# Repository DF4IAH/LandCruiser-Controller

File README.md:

# LandCruiser-Controller
µP controller for enabling LandCruisers for special tail-gates, alarms and multiple other features based on ATmega328P. Hardware (EAGLE), Software and Documentation is included.

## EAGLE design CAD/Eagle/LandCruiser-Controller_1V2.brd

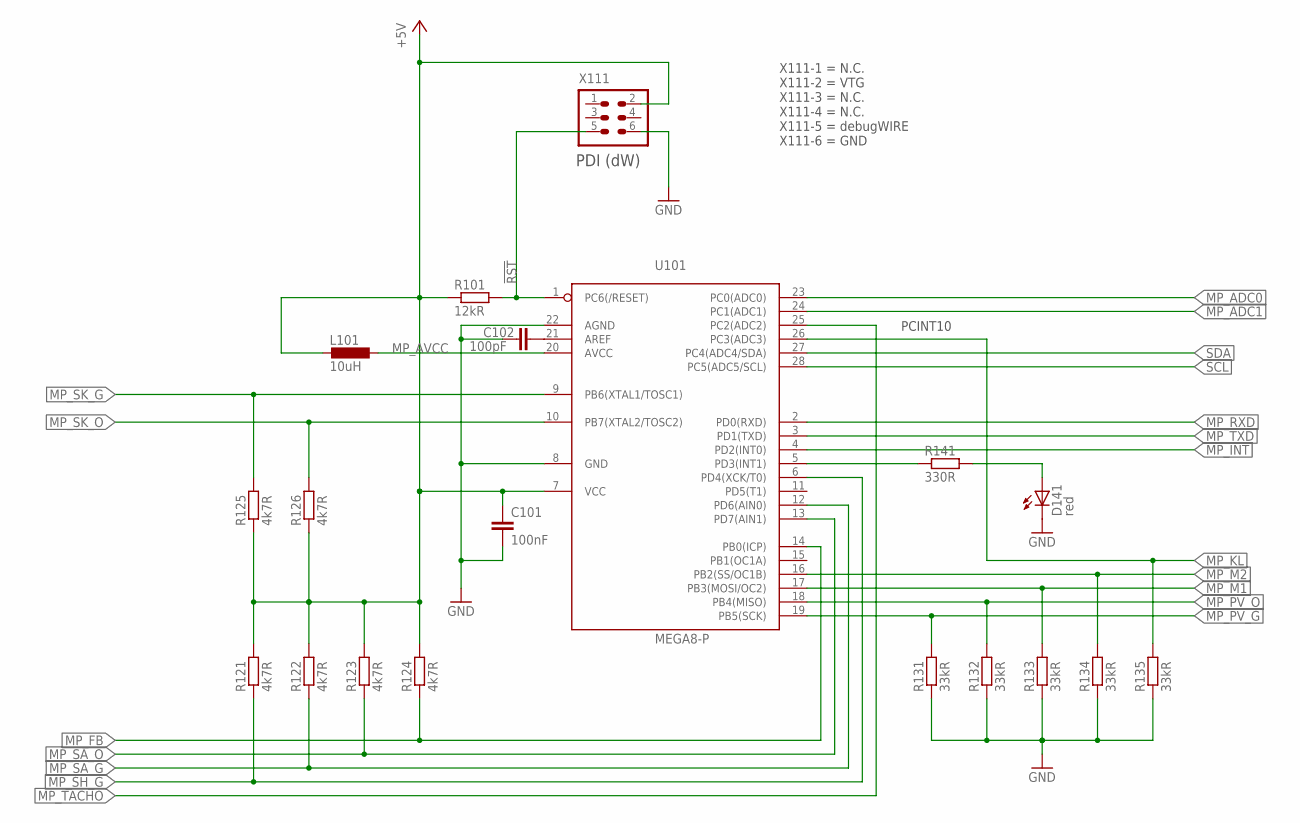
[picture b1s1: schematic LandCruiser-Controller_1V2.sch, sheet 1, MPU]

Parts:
C101: 100nF; C0805
C102: 100pF; C0805
D141: red; LED_2PIN-TTH
L101: 10uH; L1812
R101: 12kR; R0805
R121, R122, R123, R124, R125, R126: 4k7R; R0805
R131, R132, R133, R134, R135: 33kR; R0805
R141: 330R; R0805
U101: MEGA8-P; DIL28-3
X111: HEADER-2X3; 2X03

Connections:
!RST: R101.2, U101.1 (PC6(/RESET)), X111.5
+5V: C101.1, L101.2, R101.1, R121.2, R122.2, R123.2, R124.2, R125.1, R126.1, U101.7 (VCC), X111.2; also elsewhere on the board
GND: C101.2, C102.1, D141.C, R131.1, R132.1, R133.1, R134.1, R135.1, U101.8 (GND), U101.22 (AGND), X111.6; also elsewhere on the board
LED_A: D141.A, R141.2
MP_ADC0: U101.23 (PC0(ADC0)); also elsewhere on the board
MP_ADC1: U101.24 (PC1(ADC1))
MP_AREF: C102.2, U101.21 (AREF)
MP_AVCC: L101.1, U101.20 (AVCC)
MP_FB: R124.1, U101.14 (PB0(ICP)); also elsewhere on the board
MP_INT: U101.4 (PD2(INT0))
MP_KL: R135.2, U101.26 (PC3(ADC3)); also elsewhere on the board
MP_LED: R141.1, U101.5 (PD3(INT1))
MP_M1: R133.2, U101.17 (PB3(MOSI/OC2)); also elsewhere on the board
MP_M2: R134.2, U101.16 (PB2(SS/OC1B)); also elsewhere on the board
MP_PV_G: R131.2, U101.19 (PB5(SCK)); also elsewhere on the board
MP_PV_O: R132.2, U101.18 (PB4(MISO)); also elsewhere on the board
MP_RXD: U101.2 (PD0(RXD)); also elsewhere on the board
MP_SA_G: R122.1, U101.12 (PD6(AIN0)); also elsewhere on the board
MP_SA_O: R123.1, U101.13 (PD7(AIN1)); also elsewhere on the board
MP_SH_G: R121.1, U101.6 (PD4(XCK/T0)); also elsewhere on the board
MP_SK_G: R125.2, U101.9 (PB6(XTAL1/TOSC1)); also elsewhere on the board
MP_SK_O: R126.2, U101.10 (PB7(XTAL2/TOSC2)); also elsewhere on the board
MP_TACHO: U101.25 (PC2(ADC2)); also elsewhere on the board
MP_TXD: U101.3 (PD1(TXD)); also elsewhere on the board
SCL: U101.28 (PC5(ADC5/SCL)); also elsewhere on the board
SDA: U101.27 (PC4(ADC4/SDA)); also elsewhere on the board

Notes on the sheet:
PDI (dW)
X111-1 = N.C. X111-2 = VTG X111-3 = N.C. X111-4 = N.C. X111-5 = debugWIRE X111-6 = GND
PCINT10

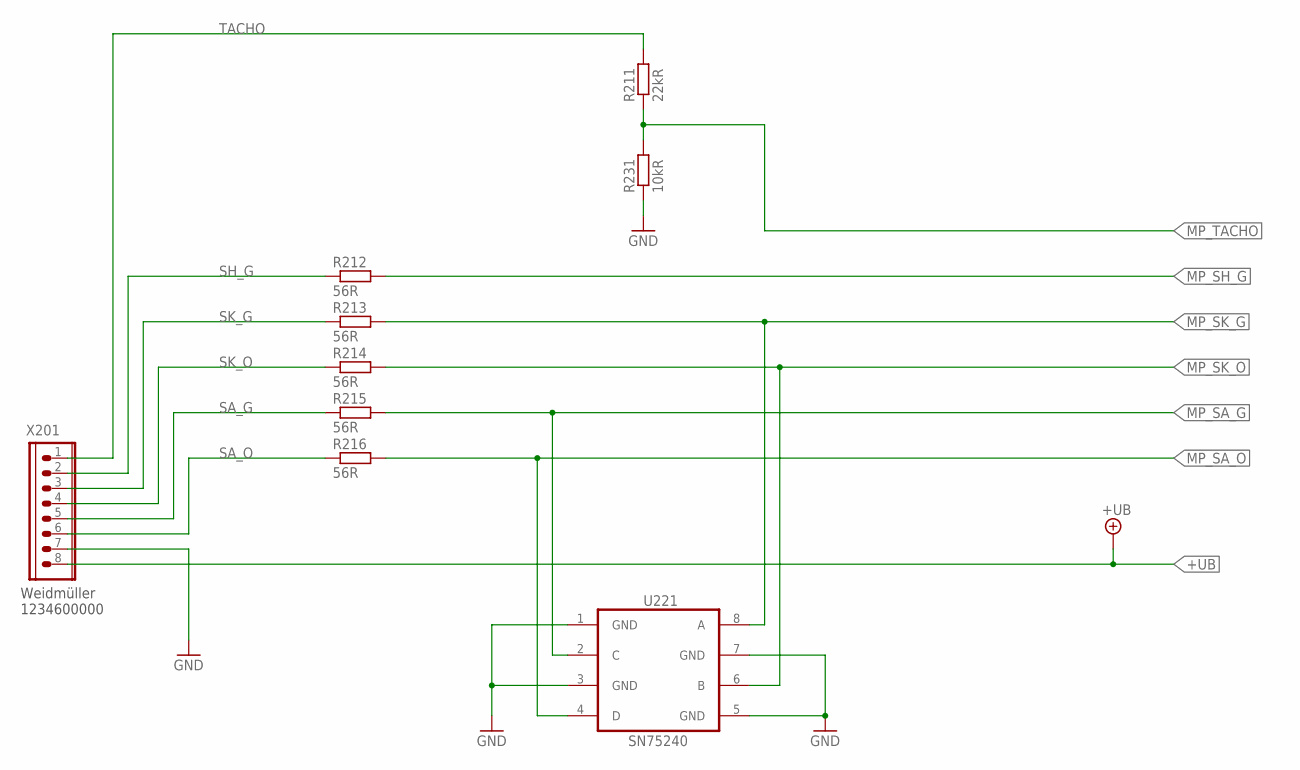
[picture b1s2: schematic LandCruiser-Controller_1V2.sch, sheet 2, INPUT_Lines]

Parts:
R211: 22kR; R0805
R212, R213, R214, R215, R216: 56R; R0805
R231: 10kR; R0805
U221: SN75240; TSSOP-8
X201: WEIDMUELLER 1234600000; WIRE-TO-BOARD_5MM08_1X08

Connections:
+UB: X201.8; also elsewhere on the board
GND: R231.1, U221.1 (GND), U221.3 (GND), U221.5 (GND), U221.7 (GND), X201.7; also elsewhere on the board
MP_SA_G: R215.2, U221.2 (C); also elsewhere on the board
MP_SA_O: R216.2, U221.4 (D); also elsewhere on the board
MP_SH_G: R212.2; also elsewhere on the board
MP_SK_G: R213.2, U221.8 (A); also elsewhere on the board
MP_SK_O: R214.2, U221.6 (B); also elsewhere on the board
MP_TACHO: R211.1, R231.2; also elsewhere on the board
SA_G: R215.1, X201.5
SA_O: R216.1, X201.6
SH_G: R212.1, X201.2
SK_G: R213.1, X201.3
SK_O: R214.1, X201.4
TACHO: R211.2, X201.1

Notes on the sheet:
Weidmüller 1234600000

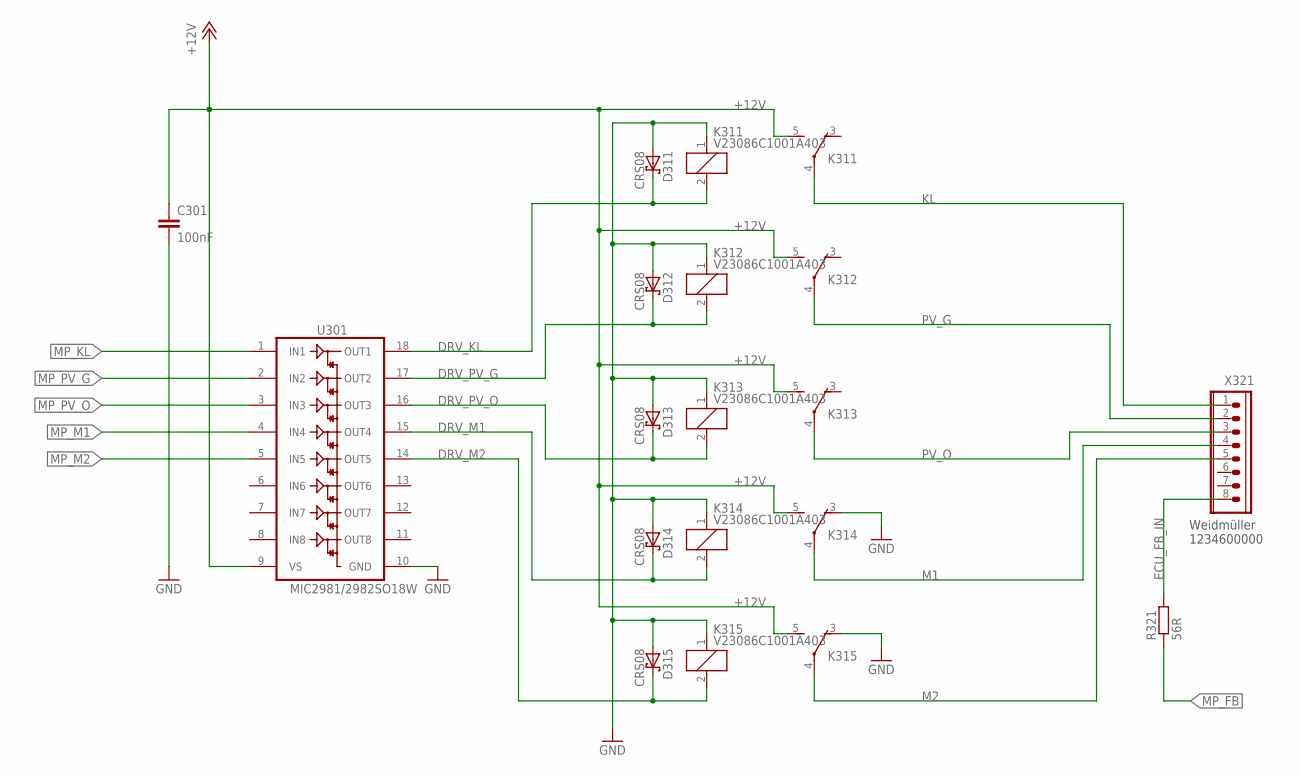
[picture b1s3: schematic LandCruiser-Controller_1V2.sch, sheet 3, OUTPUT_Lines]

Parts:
C301: 100nF; C0805
D311, D312, D313, D314, D315: CRS08; SOD80C
K311, K312, K313, K314, K315: V23086C1001A403; V23086-CO
R321: 56R; R0805
U301: MIC2981/2982SO18W; SO-18W
X321: WEIDMUELLER 1234600000; WIRE-TO-BOARD_5MM08_1X08

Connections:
+12V: C301.1, K311.5 (S), K312.5 (S), K313.5 (S), K314.5 (S), K315.5 (S), U301.9 (VS); also elsewhere on the board
DRV_KL: D311.C, K311.2, U301.18 (OUT1)
DRV_M1: D314.C, K314.2, U301.15 (OUT4)
DRV_M2: D315.C, K315.2, U301.14 (OUT5)
DRV_PV_G: D312.C, K312.2, U301.17 (OUT2)
DRV_PV_O: D313.C, K313.2, U301.16 (OUT3)
ECU_FB_IN: R321.2, X321.8
GND: C301.2, D311.A, D312.A, D313.A, D314.A, D315.A, K311.1, K312.1, K313.1, K314.1, K314.3 (O), K315.1, K315.3 (O), U301.10 (GND); also elsewhere on the board
KL: K311.4, X321.1
M1: K314.4, X321.4
M2: K315.4, X321.5
MP_FB: R321.1; also elsewhere on the board
MP_KL: U301.1 (IN1); also elsewhere on the board
MP_M1: U301.4 (IN4); also elsewhere on the board
MP_M2: U301.5 (IN5); also elsewhere on the board
MP_PV_G: U301.2 (IN2); also elsewhere on the board
MP_PV_O: U301.3 (IN3); also elsewhere on the board
PV_G: K312.4, X321.2
PV_O: K313.4, X321.3

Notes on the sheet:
Weidmüller 1234600000

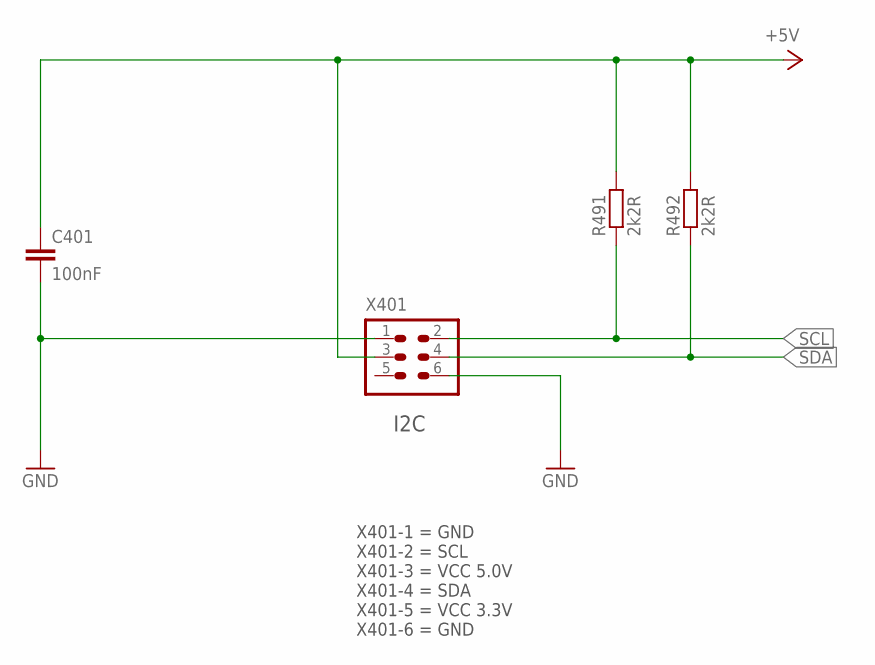
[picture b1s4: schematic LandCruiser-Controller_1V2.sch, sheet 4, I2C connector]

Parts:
C401: 100nF; C0805
R491, R492: 2k2R; R0805
X401: I2C; 2X03

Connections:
+5V: C401.1, R491.2, R492.2, X401.3; also elsewhere on the board
GND: C401.2, X401.1, X401.6; also elsewhere on the board
SCL: R491.1, X401.2; also elsewhere on the board
SDA: R492.1, X401.4; also elsewhere on the board

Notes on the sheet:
I2C
X401-1 = GND X401-2 = SCL X401-3 = VCC 5.0V X401-4 = SDA X401-5 = VCC 3.3V X401-6 = GND

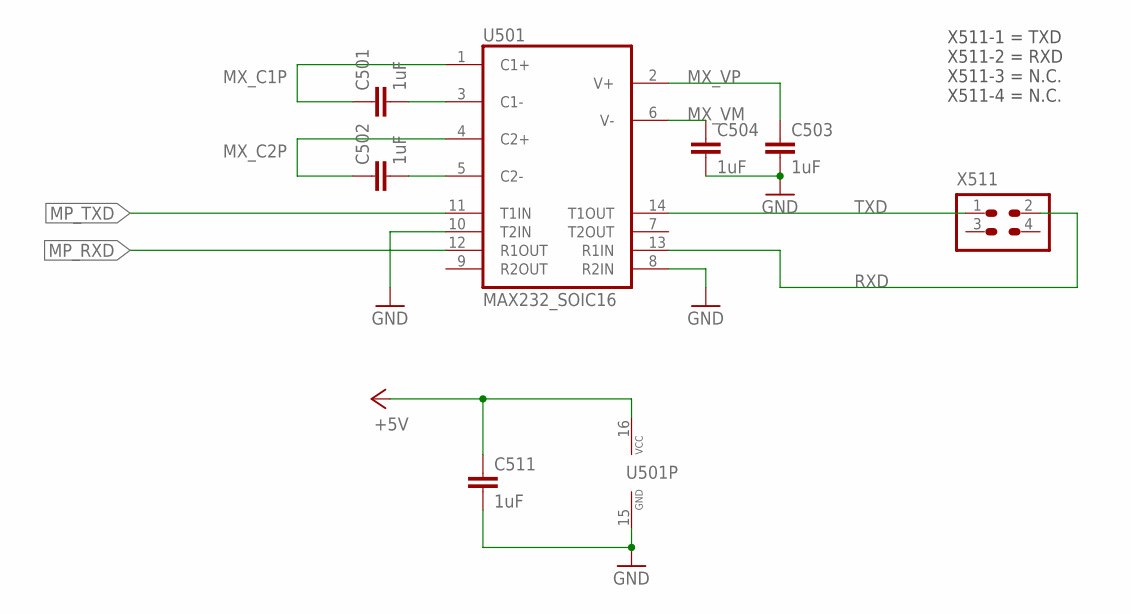
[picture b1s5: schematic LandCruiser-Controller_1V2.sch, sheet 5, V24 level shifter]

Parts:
C501, C502, C503, C504, C511: 1uF; C0805
U501: MAX232_SOIC16; SOIC16N
X511: HEADER-2X2; 2X02

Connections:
+5V: C511.1, U501.16 (VCC); also elsewhere on the board
GND: C503.2, C504.2, C511.2, U501.8 (R2IN), U501.10 (T2IN), U501.15 (GND); also elsewhere on the board
MP_RXD: U501.12 (R1OUT); also elsewhere on the board
MP_TXD: U501.11 (T1IN); also elsewhere on the board
MX_C1N: C501.2, U501.3 (C1-)
MX_C1P: C501.1, U501.1 (C1+)
MX_C2M: C502.2, U501.5 (C2-)
MX_C2P: C502.1, U501.4 (C2+)
MX_VM: C504.1, U501.6 (V-)
MX_VP: C503.1, U501.2 (V+)
RXD: U501.13 (R1IN), X511.2
TXD: U501.14 (T1OUT), X511.1

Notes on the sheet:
X511-1 = TXD X511-2 = RXD X511-3 = N.C. X511-4 = N.C.

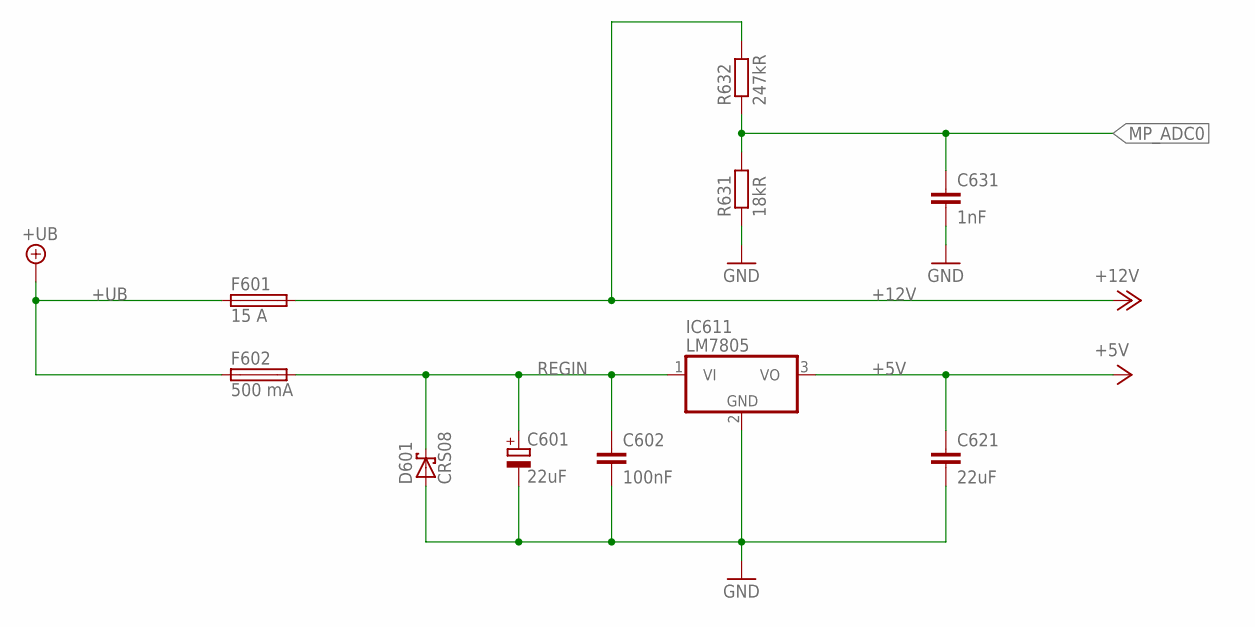
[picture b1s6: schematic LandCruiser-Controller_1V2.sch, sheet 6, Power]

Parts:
C601: 22uF; E2,5-7
C602: 100nF; C0805
C621: 22uF; C0805
C631: 1nF; C0805
D601: CRS08; SOD80C
F601: 15 A; MCCQ-121
F602: 500 mA; MCCQ-121
IC611: LM7805; TO220H
R631: 18kR; R0805
R632: 247kR; R0805

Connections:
+5V: C621.1, IC611.3 (VO); also elsewhere on the board
+12V: F601.3 (2), F601.4 (2), R632.2; also elsewhere on the board
+UB: F601.1, F601.2 (1), F602.1, F602.2 (1); also elsewhere on the board
GND: C601.-, C602.2, C621.2, C631.2, D601.A, IC611.2 (GND), R631.1; also elsewhere on the board
MP_ADC0: C631.1, R631.2, R632.1; also elsewhere on the board
REGIN: C601.+, C602.1, D601.C, F602.3 (2), F602.4 (2), IC611.1 (VI)

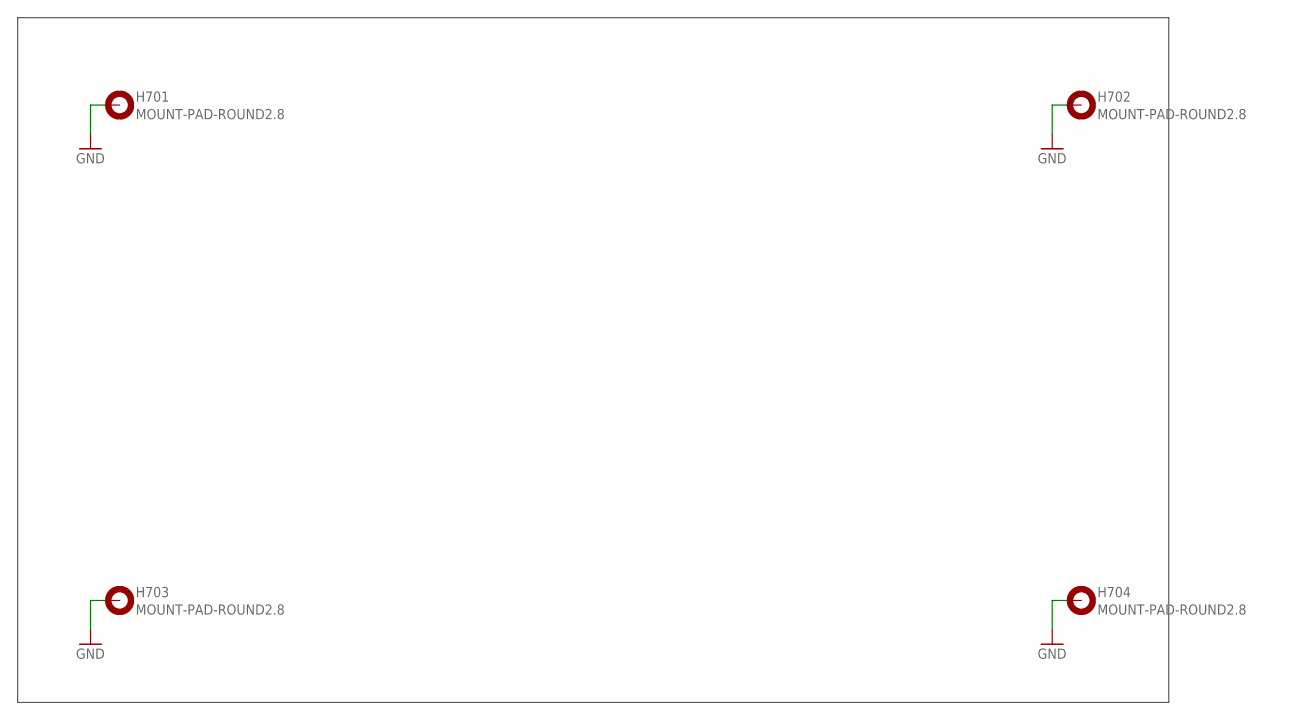
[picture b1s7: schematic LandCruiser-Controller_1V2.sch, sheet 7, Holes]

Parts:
H701, H702, H703, H704: MOUNT-PAD-ROUND2.8; 2,8-PAD

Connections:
GND: H701.B2,8, H702.B2,8, H703.B2,8, H704.B2,8; also elsewhere on the board

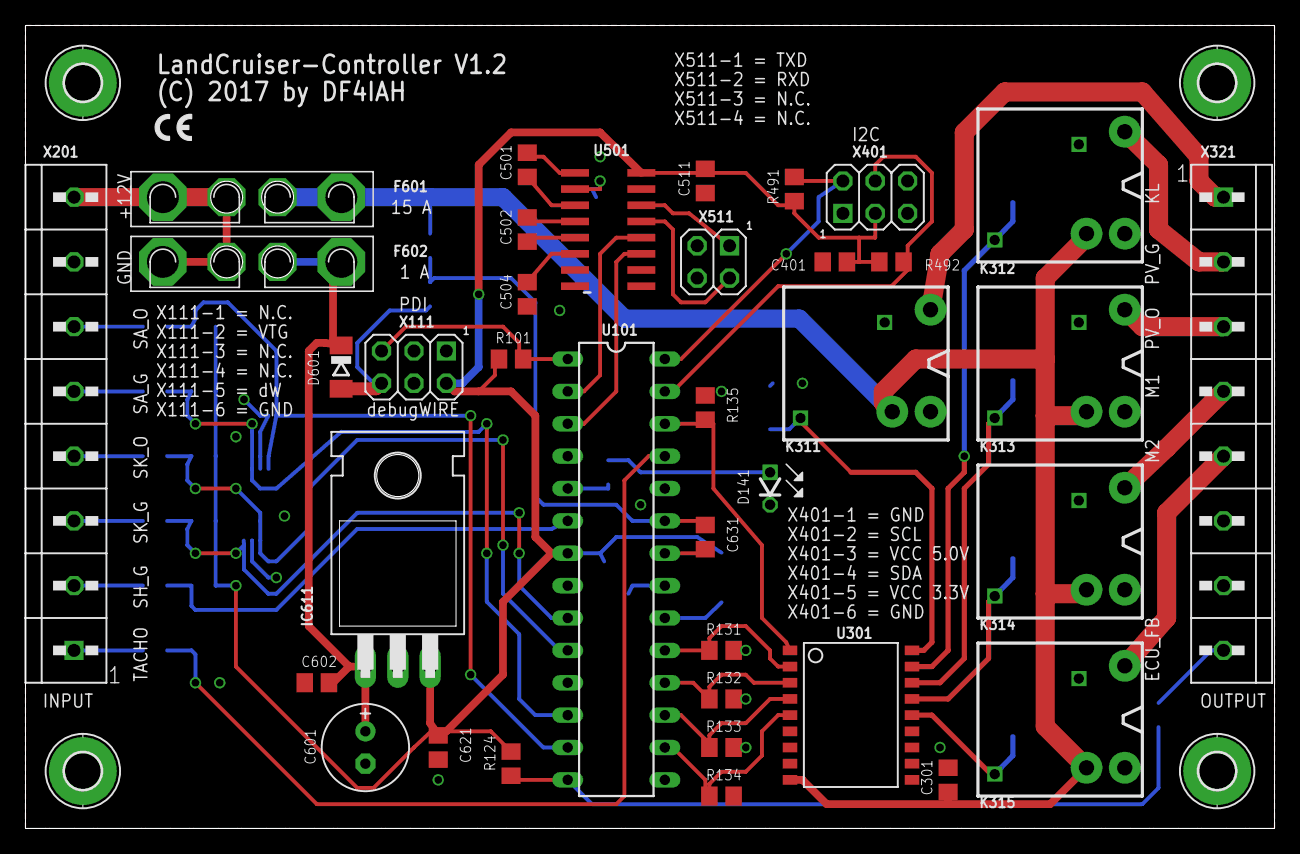
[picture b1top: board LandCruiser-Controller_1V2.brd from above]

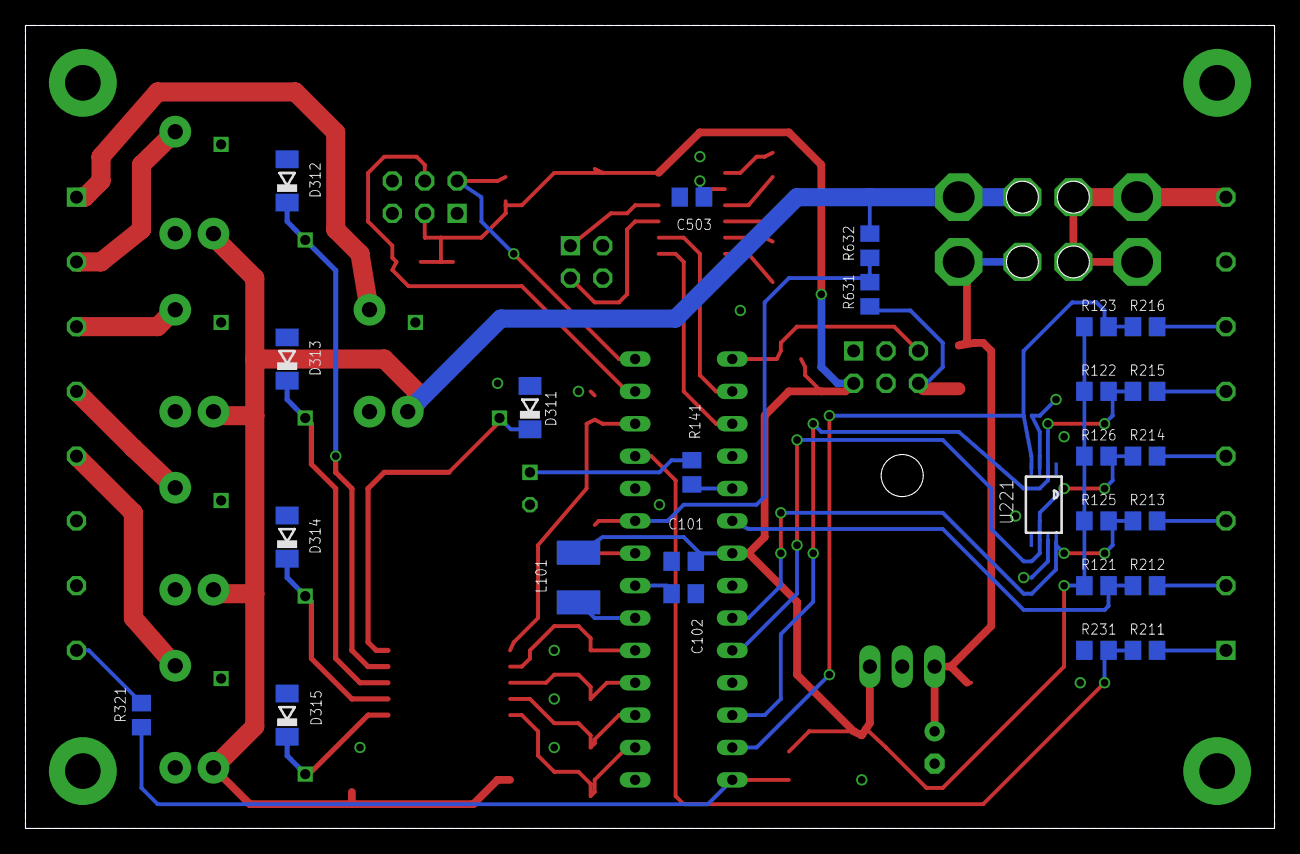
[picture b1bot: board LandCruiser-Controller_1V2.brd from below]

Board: 2 copper layers, 98.0 x 63.0 mm, 67 parts (26 on the bottom side), 52 nets.

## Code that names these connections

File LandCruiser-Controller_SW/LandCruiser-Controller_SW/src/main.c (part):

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	 * most critical pins are handled first.
	 */

	DDRB  = 0b00111100;											// Out: PB5: MP_PV_G, PB4: MP_PV_O, PB3: MP_M1, PB2: MP_M2
	PORTB = 0b11000011;											// In:  PB7: MP_SK_O, PB6: MP_SK_G, PB1: NC, PB0: SH_G

	DDRC  = 0b00101000;											// Out: PC5: SCL, PC3: MP_KL
	PORTC = 0b00110000;											// In:  PC4: SDA, PC2: MP_TACHO (PCINT10), PC1: MP_ADC1, PC0: MP_ADC0

	DDRD  = 0b00001010;											// Out: PD3: MP_LED, PD1: MP_TXD
	PORTD = 0b11110111;											// In:  PD7: MP_SA_O, PD6: MP_SA_G, PD5: NC, PD4: MP_FB, PD2: MP_INT, PD0: MP_RXD

	/* Connect PCINT10 = Pin PC2 to PCI1 */
	PCMSK1	= _BV(PCINT10);
	PCIFR	= _BV(PCIF1);
	PCICR	= _BV(PCIE1);
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
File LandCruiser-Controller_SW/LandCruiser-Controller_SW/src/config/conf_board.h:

/**
 * \file
 *
 * \brief User board configuration template
 *
 */
/*
 * Support and FAQ: visit <a href="http://www.atmel.com/design-support/">Atmel Support</a>
 */

#ifndef CONF_BOARD_H
#define CONF_BOARD_H

#define FB_GPIO							IOPORT_CREATE_PIN(PORTB, 0)
#define XXXB1_GPIO						IOPORT_CREATE_PIN(PORTB, 1)
#define M2_GPIO							IOPORT_CREATE_PIN(PORTB, 2)
#define M1_GPIO							IOPORT_CREATE_PIN(PORTB, 3)
#define PV_O_GPIO						IOPORT_CREATE_PIN(PORTB, 4)
#define PV_G_GPIO						IOPORT_CREATE_PIN(PORTB, 5)
#define SK_G_GPIO						IOPORT_CREATE_PIN(PORTB, 6)
#define SK_O_GPIO						IOPORT_CREATE_PIN(PORTB, 7)

#define ADC_12V_GPIO					IOPORT_CREATE_PIN(PORTC, 0)
#define ADC1_GPIO						IOPORT_CREATE_PIN(PORTC, 1)
#define TACHO_GPIO						IOPORT_CREATE_PIN(PORTC, 2)
#define KL_GPIO							IOPORT_CREATE_PIN(PORTC, 3)
#define SDA_GPIO						IOPORT_CREATE_PIN(PORTC, 4)
#define SCL_GPIO						IOPORT_CREATE_PIN(PORTC, 5)

#define RXD_GPIO						IOPORT_CREATE_PIN(PORTD, 0)
#define TXD_GPIO						IOPORT_CREATE_PIN(PORTD, 1)
#define INT_GPIO						IOPORT_CREATE_PIN(PORTD, 2)
#define LED_GPIO						IOPORT_CREATE_PIN(PORTD, 3)
#define SH_G_GPIO						IOPORT_CREATE_PIN(PORTD, 4)
#define XXXD5_GPIO						IOPORT_CREATE_PIN(PORTD, 5)
#define SA_G_GPIO						IOPORT_CREATE_PIN(PORTD, 6)
#define SA_O_GPIO						IOPORT_CREATE_PIN(PORTD, 7)

#endif // CONF_BOARD_H

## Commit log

2017-08-23 DOCS - Docs directory added
2017-08-23 HW_V1.0 - CAD directory added
2017-08-23 SW - LandCruiser-Controller_SW directory added
2017-08-23 SW - initial project set-up
2017-08-24 DOCS - first ideas for realization added
2017-08-24 HW_V1.0 - initial hardware set-up
2017-08-25 HW - pull-down resistors added to the ATmega output lines
2017-08-25 SW - I/O settings done, TC1 timer running with 1 kHz overflow frequency
2017-08-26 SW - FSM - finite state machine prepared for coding
2017-08-26 SW - FSM - simple schema without intermediate change of direction OK
2017-08-26 SW - avrdude - scripts for erasing, burning fuses, EEPROM and FLASH expanded
2017-08-26 SW - binaries added
2017-08-26 HW - pull-up resistors added to the ATmega input lines
2017-08-27 SW - FSM - now working with ne-noising and direction reversal
2017-08-27 SW - FSM - fix added for the case S-K_O opens during arms are not in close position
2017-08-27 HW - Linear voltage regulator 7805 added
2017-08-28 DOCS - Datasheets 91_Wire-to-Board-Connectors - added
2017-08-28 HW - Wire-to-Board connectors added
2017-08-29 DOCS - 20_Datasheets - ESD - SN75240PWR added
2017-08-29 HW_V1.0 - ESD - circuits added
2017-08-29 HW_V1.0 - Driver - circuit added
2017-08-29 HW_V1.0 - Relay - pre-works done
2017-08-29 HW - V24 level shifter - new page with frame added
2017-08-30 HW_V1.0 - MPU - AVCC with 10uH for better ADC results
2017-08-30 HW_V1.0 - OUTPUT - relay units added
2017-08-30 DOCS - Fuses - multicomp MCCQ-121 added
2017-08-30 HW_V1.0 - V24 level shifter connected, Tacho input signal added
2017-08-31 DOCS - RS232 - TI MAX232 SOIC-16 added
2017-08-31 DOCS - RS232 - directory name changed from Serial to RS232
2017-08-31 HW_V1.0 - changed most devices to SMD variants
2017-08-31 HW_V1.0 - df4iah_fuse.lbr - trying to fix the restring issue
2017-08-31 HW_V1.0 - Place&Routing - placement done, half of the routing done
2017-09-01 HW_V1.0 - Routing - routing finished, no ground polygone here
2017-09-01 HW_V1.0 - Routing - now with ground polygone
2017-09-01 HW_V1.0 - Routing - GND vias added, place below the LM7805 cleared
2017-09-01 HW_V1.0 - additional capacitors added
2017-09-02 HW_V1.0 - status LED added, ADC0 connected to 15:1 divider for 12V control
2017-09-03 HW_V1.0 - dimension values rounded, pad below the LM7805 restricted
2017-09-03 HW_V1.0 - fuse drillings added - V1.0 finished and ordered
2017-09-03 HW_V1.1 - new version added
2017-09-03 SW - LED and ADC0/ADC1 channels added
2017-09-04 DOCS - Mouser distributor added
2017-09-06 SW - ADC0/Temp - measurements and calculations fixed
2017-09-07 SW - ADC0 - under-voltage detection added
2017-09-08 SW - over-speed detection added
2017-09-09 SW - over-speed detection fixed
2017-09-09 SW - FSM - pre-requests removed
2017-09-16 SW - Status LED for counting seconds added
2017-10-17 HW_V1.1 - driver switches against ground, not Vbat. Another input line added.
2017-10-19 SW - LED blink codes added, FSM states now blink code values
2017-10-27 SW - LED blink codes added, FSM states now blink code values (2)
2017-10-30 SW - UART output by 38,400 baud 8N1
2017-11-01 SW - FSM state, input vector and output vector changes are reported via UART
2017-11-01 SW - switched FB input with rear tail gate (SH_G)
2017-11-01 HW_V1.1 - switched FB input with rear tail gate (SH_G)
2017-12-10 HW_V1.2 - new version added
2017-12-10 HW_V1.0 - again included in master branch
2017-12-10 HW_V1.1 - again included in master branch
2017-12-10 SW - ADC fixed, FSM fixed, ready-to-run
2017-12-18 SW - increase speed of contacts to stop any movement at once - to be tested
2017-12-22 SW - timing constant for loop iterations changed 50ms --> 10ms
2018-02-01 SW - broken LED code fixed
2018-02-02 SW - remove wrong include file
2018-02-02 SW - negation of the tailgate close signal, silence time before lockers do activate
2018-02-03 SW - not needed waiting times removed, minor changes done

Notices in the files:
CAD/Eagle/LandCruiser-Controller_1V2.brd:
(C) 2017 by DF4IAH
